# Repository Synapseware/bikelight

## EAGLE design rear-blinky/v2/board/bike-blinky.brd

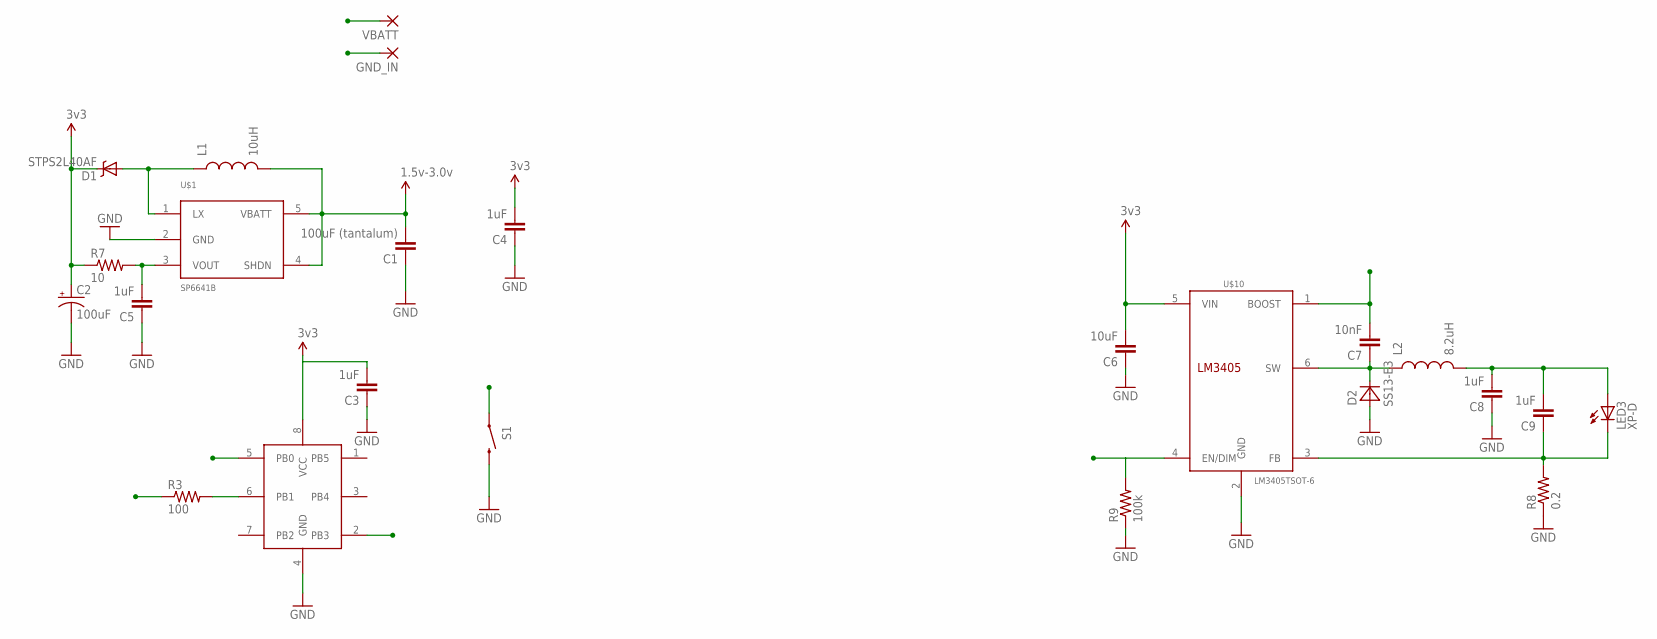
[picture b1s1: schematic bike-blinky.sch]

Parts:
C1: 100uF (tantalum); 1206
C2: 100uF; PANASONIC_C
C3, C4, C5, C8, C9: 1uF; 0603-CAP
C6: 10uF; 1206
C7: 10nF; 0603-CAP
D1: STPS2L40AF; SMA-DIODE
D2: SS13-E3; SMA
GND_IN: WIREPAD2,54/1,0; 2,54/1,0
L1: 10uH; 1007
L2: 8.2uH; 1210
LED3: XP-D; XB-D-REV1
R3: 100; 0603-RES
R7: 10; 0603-RES
R8: 0.2; R2010
R9: 100k; 0603-RES
S1: SWITCH-MOMENTARY-2SMD-2; TACTILE_SWITCH_SMD-2
U$1: SP6641B; SOT23-5
U$2: ATTINY13; WSOIC-8
U$10: LM3405TSOT-6; TSOT-6
VBATT: WIREPAD2,54/1,0; 2,54/1,0

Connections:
5V: C2.+, C3.2, C4.2, C6.2, D1.C, R7.1, U$2.8 (VCC), U$10.5 (VIN)
ENABLE: C7.2, U$2.2 (PB3), U$10.1 (BOOST)
GND: C1.1, C2.-, C3.1, C4.1, C5.1, C6.1, C8.1, D2.A, GND_IN.1, R8.1, R9.1, S1.1 (2), U$1.2 (GND), U$2.4 (GND), U$10.2 (GND)
unnamed: R3.2, U$2.6 (PB1)
unnamed: D1.A, L1.1, U$1.1 (LX)
unnamed: C5.2, R7.2, U$1.3 (VOUT)
unnamed: C9.1, LED3.C, R8.2, U$10.3 (FB)
unnamed: C7.1, D2.C, L2.1, U$10.6 (SW)
unnamed: C8.2, C9.2, L2.2, LED3.A
RED: R3.1, R9.2, U$10.4 (EN/DIM)
SW: S1.2 (1), U$2.5 (PB0)
VBATT: C1.2, L1.2, U$1.4 (SHDN), U$1.5 (VBATT), VBATT.1

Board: 2 copper layers, 24 parts (0 on the bottom side), 12 nets, no tracks yet.

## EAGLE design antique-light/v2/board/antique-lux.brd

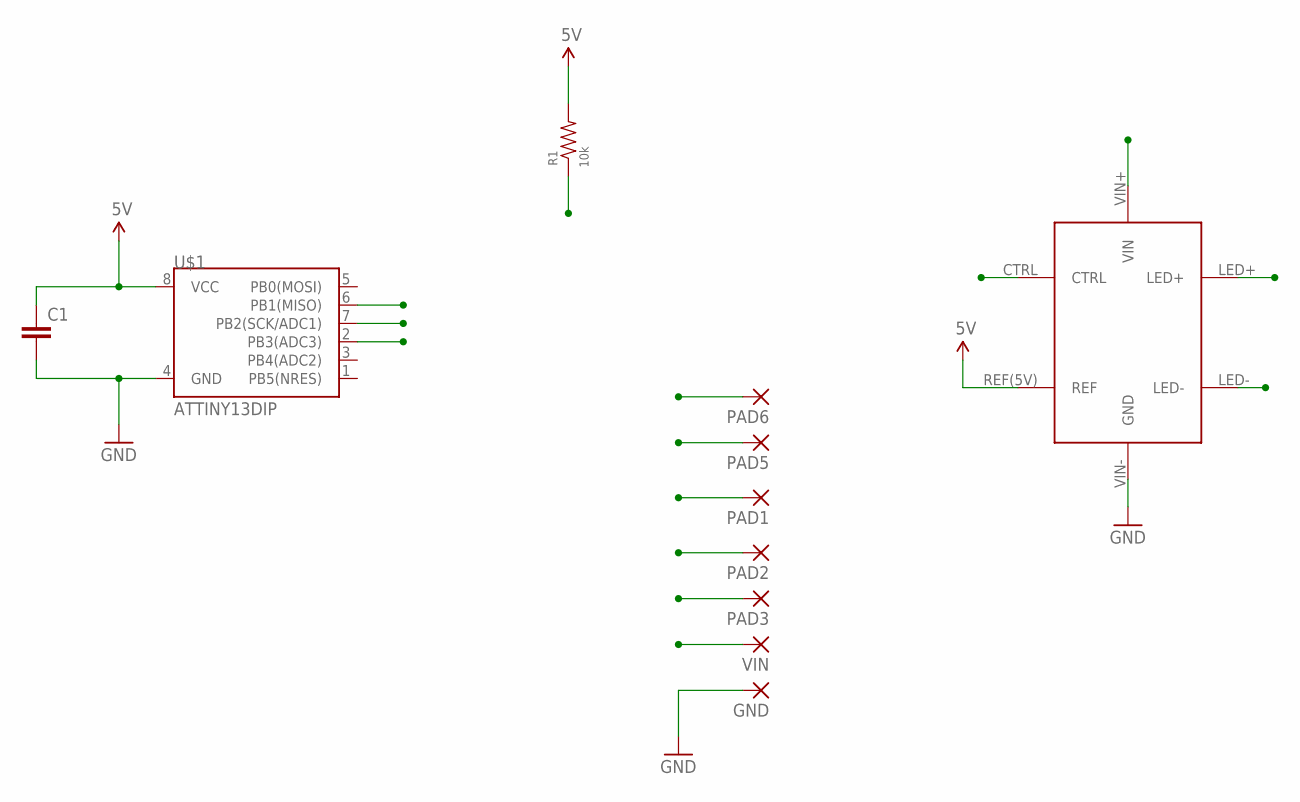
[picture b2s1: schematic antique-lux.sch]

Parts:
C1: CAPEZ; CAP-PTH-SMALLEZ
GND: WIREPAD2,54/0,8; 2,54/0,8
PAD1, PAD2, PAD3, PAD5, PAD6: WIREPAD2,54/0,8; 2,54/0,8
R1: 10k; VERT-PTH
U$1: ATTINY13DIP; DIP08
U$2: LUXDRIVE-PINNED; LUXDRIVE-BUCKPUCK-PINNED
VIN: WIREPAD2,54/0,8; 2,54/0,8

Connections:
5V: C1.1, R1.2, U$1.8 (VCC), U$2.REF(5V) (REF)
CTRL: R1.1, U$1.6 (PB1(MISO)), U$2.CTRL
GND: C1.2, GND.1, PAD6.1, U$1.4 (GND), U$2.VIN- (GND)
LED+: PAD2.1, U$2.LED+
LED-: PAD3.1, U$2.LED-
PWR_LED: PAD1.1, U$1.2 (PB3(ADC3))
SW_IN: PAD5.1, U$1.7 (PB2(SCK/ADC1))
VIN: U$2.VIN+ (VIN), VIN.1

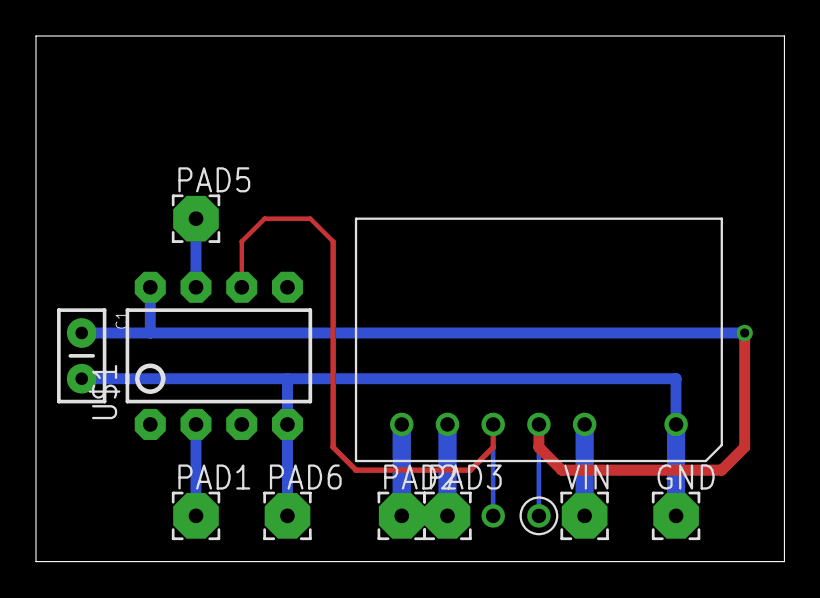
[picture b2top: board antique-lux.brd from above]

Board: 2 copper layers, 41.6 x 29.2 mm, 11 parts (0 on the bottom side), 8 nets.

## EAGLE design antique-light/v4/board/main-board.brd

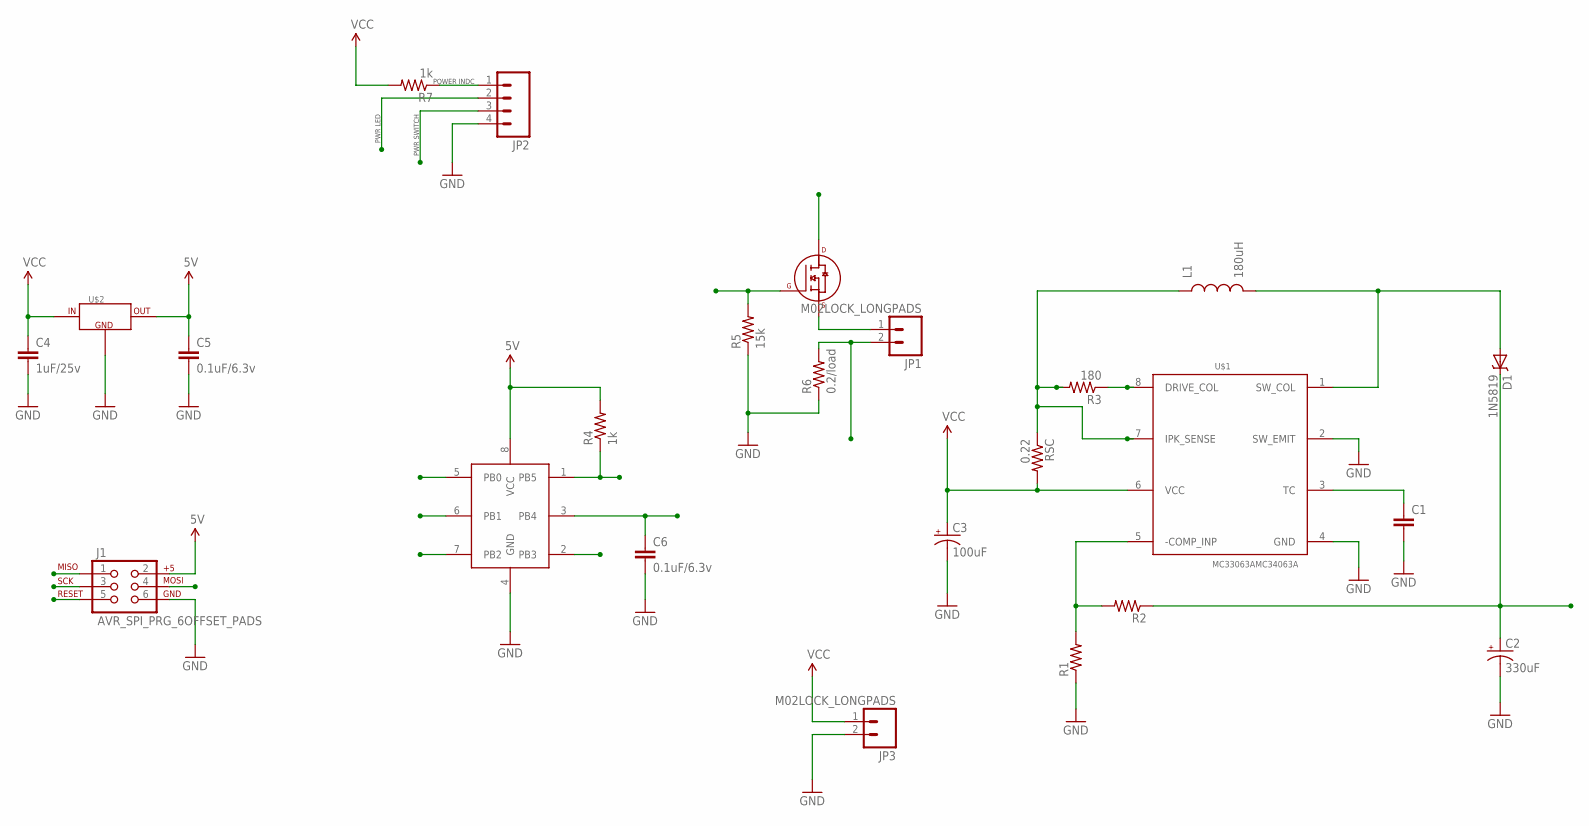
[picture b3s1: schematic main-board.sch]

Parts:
C1: CAP0603-CAP; 0603-CAP
C2: 330uF; PANASONIC_D
C3: 100uF; PANASONIC_D
C4: 1uF/25v; 0603-CAP
C5, C6: 0.1uF/6.3v; 0603-CAP
D1: 1N5819; SMA-DIODE
J1: AVR_SPI_PRG_6OFFSET_PADS; 2X3_OFFSET
JP1, JP3: M02LOCK_LONGPADS; 1X02_LOCK_LONGPADS
JP2: M04LONGPADS; 1X04_LONGPADS
L1: 180uH; CDRH125
R1, R2: RESISTOR0603; 0603-RES
R3: 180; 0603-RES
R4, R7: 1k; 0603-RES
R5: 15k; 0603-RES
R6: 0.2/load; 0805
RSC: 0.22; 0603-RES
U$1: MC33063AMC34063A; SOIC-8
U$2: TPS715XX; SC70-5
U$3: ATTINY13; WSOIC-8
U$4: FQB30N06LTM; TO-263AB

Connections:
5V: C5.1, J1.2, R4.2, U$2.5 (OUT), U$3.8 (VCC)
GND: C1.2, C2.-, C3.-, C4.2, C5.2, C6.2, J1.6, JP2.4, JP3.2, R1.1, R5.1, R6.1, U$1.2 (SW_EMIT), U$1.4 (GND), U$2.2 (GND), U$3.4 (GND)
LED+: C2.+, D1.C, R2.1, U$4.4 (D)
MISO: J1.1, U$3.6 (PB1)
MOSI: J1.4, R5.2, U$3.5 (PB0), U$4.1 (G)
unnamed: R1.2, R2.2, U$1.5 (-COMP_INP)
unnamed: JP1.1, U$4.3 (S)
unnamed: JP2.1, R7.1
unnamed: L1.1, R3.2, RSC.1, U$1.7 (IPK_SENSE)
unnamed: R3.1, U$1.8 (DRIVE_COL)
unnamed: D1.A, L1.2, U$1.1 (SW_COL)
unnamed: C1.1, U$1.3 (TC)
PWR_LED: JP2.2, U$3.2 (PB3)
RESET: J1.5, R4.1, U$3.1 (PB5)
SCK: J1.3, JP2.3, U$3.7 (PB2)
SENSE: C6.1, JP1.2, R6.2, U$3.3 (PB4)
VCC: C3.+, C4.1, JP3.1, R7.2, RSC.2, U$1.6 (VCC), U$2.4 (IN)

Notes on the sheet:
POWER INDC
PWR SWITCH
PWR LED

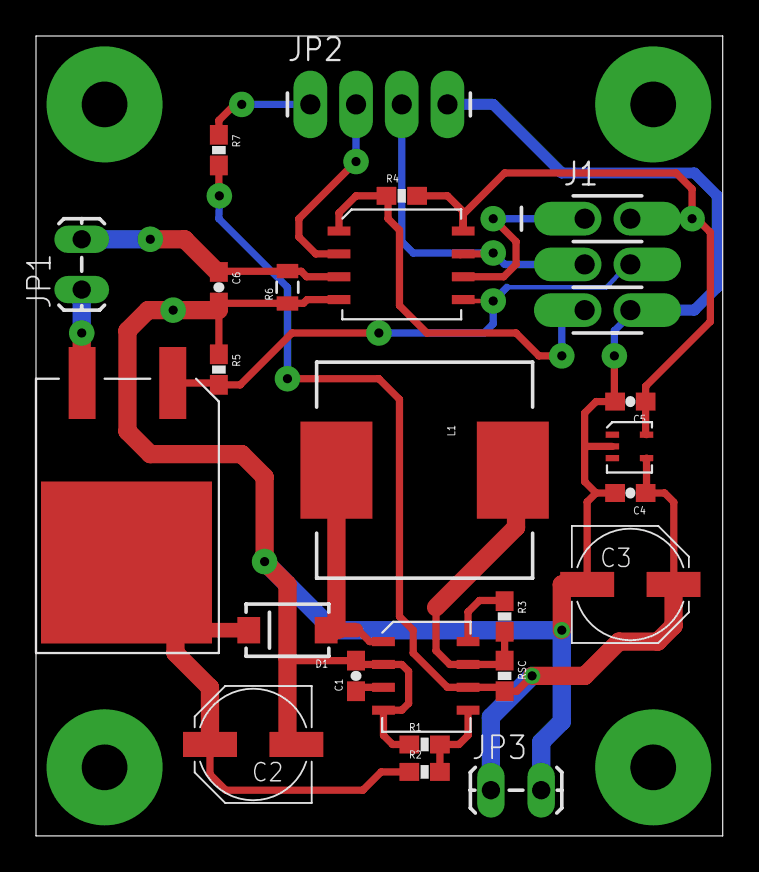
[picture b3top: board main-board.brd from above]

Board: 2 copper layers, 38.2 x 44.4 mm, 24 parts (0 on the bottom side), 17 nets.

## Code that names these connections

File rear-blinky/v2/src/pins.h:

/*
* pins.h
*
* Created: 12/31/2011 3:50:01 PM
*  Author: Matthew
*/ 


#ifndef PINS_H_
#define PINS_H_


//------------------------------------------------------------------------------------------
// Power switch
#define PWR_SW				PB0
#define pwrSwReleased()		((PORTB & (1<<PWR_SW)) != 0)
#define pwrSwPressed()		((PORTB & (1<<PWR_SW)) == 0)


//------------------------------------------------------------------------------------------
// Power LED
#define PWR_LED				PB3
#define pwrLedEnable()		DDRB	|= (1<<PWR_LED)
#define pwrLedOn()			PORTB	|= (1<<PWR_LED)
#define pwrLedOff()			PORTB	&= ~(1<<PWR_LED)
#define pwrLedTgl()			PINB	|= (1<<PWR_LED)


//------------------------------------------------------------------------------------------
// PWM output
#define PWM_REGISTER		OCR0B
#define PWM_LED				PB1
#define pwmLedEnable()		DDRB	|= (1<<PWM_LED)
#define pwmLedOff()			PORTB	&= ~(1<<PWM_LED)


#endif /* PINS_H_ */

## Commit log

2014-06-03 Copying over board layout file
2014-06-07 Cleaning up old bikelight repo
2014-06-07 Cleaning up project and moving board files to the proper location

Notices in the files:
parts and their libraries:
SparkFun-DigitalIC: Licensing: CC v3.0 Share-Alike You are welcome to use this library for commercial purposes.
